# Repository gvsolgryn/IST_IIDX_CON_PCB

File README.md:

# IST_IIDX_CON_PCB
ist 몰에서 만든 iidx 컨트롤러 PCB 딜레이가 너무 심해서 우리 기합찬 육군(만기전역)들이 설계하기로 하였다

## 기합찬 준비운동

1. 일단 KiCAD를 받는다
2. `git` 을 다운로드 받는다
3. `git clone https://github.com/gvsolgryn/IST_IIDX_CON_PCB.git` 을 하여 우리 기합찬 PCB 프로젝트를 다운로드 받는다
4. KiCAD를 실행 시킨 뒤 프로젝트를 연다
5. 불만이 있으면 KiCAD를 이용해서 PCB 다 수정해서 머지? 요청 하면 우리 기합찬 육군들이 업데이트를 해주도록 하겠다

## 악! PCB Gerber을 이용하여 PCB를 출력하고싶어 해병님!!
1. https://jlcpcb.com/ 에 방문한다
2. gerber.zip 을 Add Gerber File 에 드래그 엔 드롭 한다
3. 결제한다!

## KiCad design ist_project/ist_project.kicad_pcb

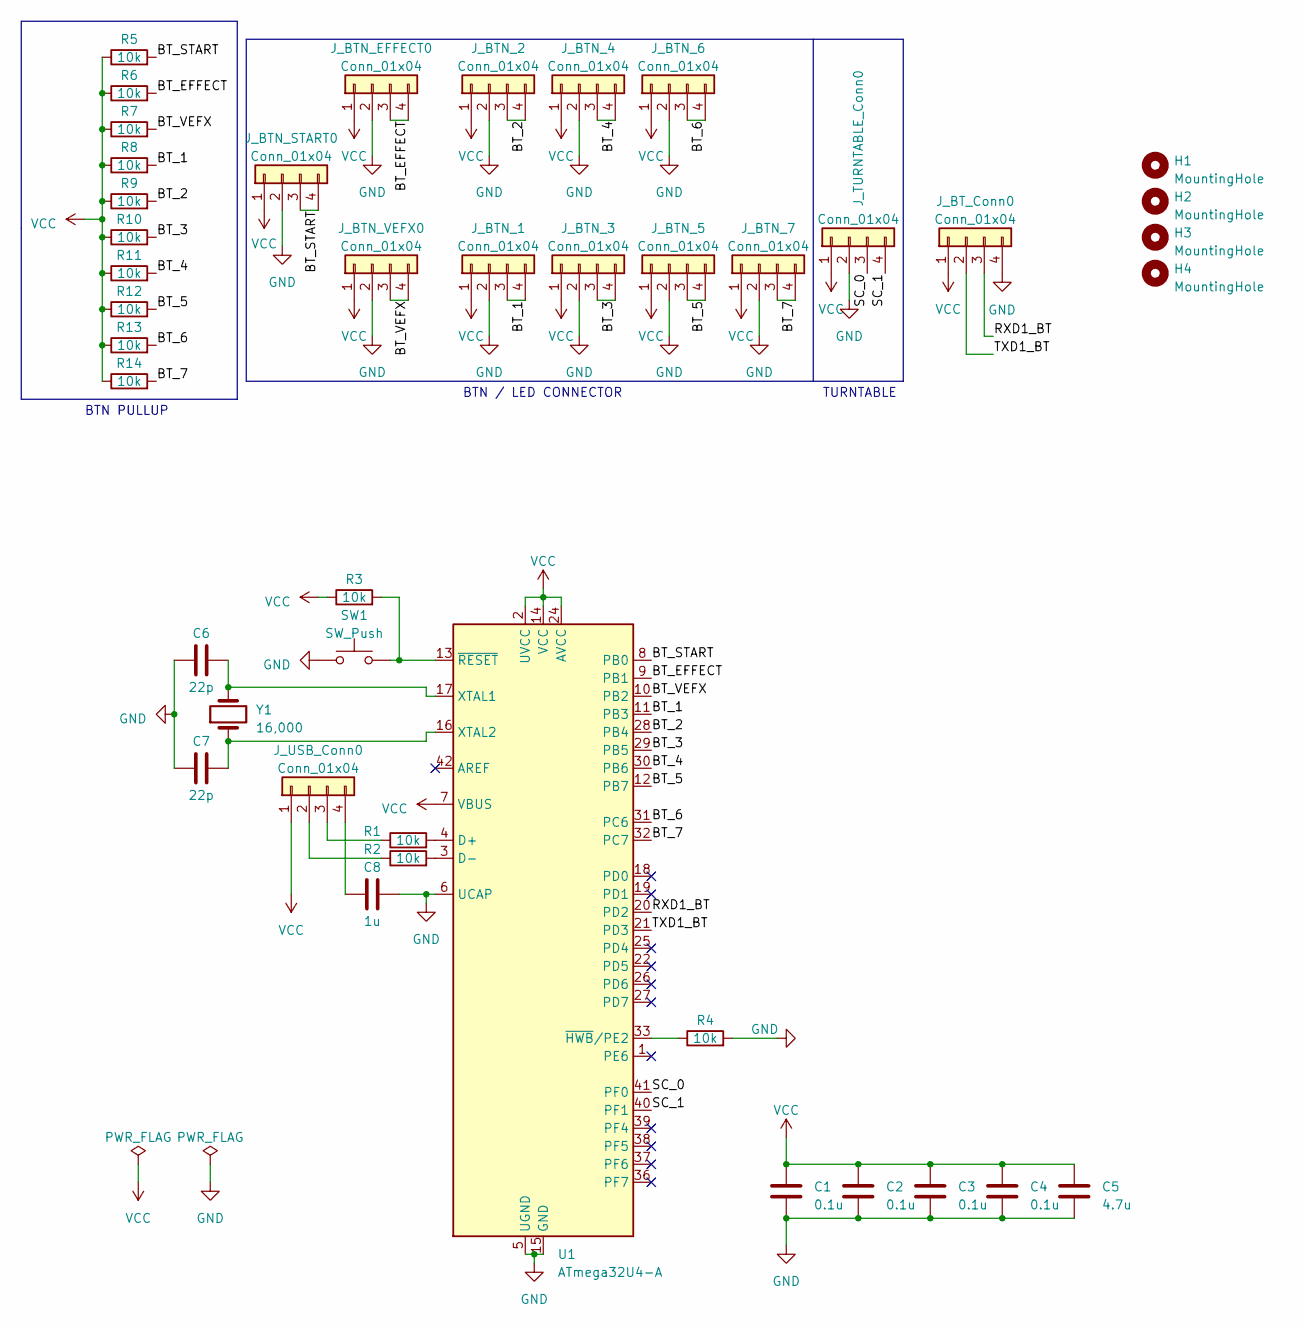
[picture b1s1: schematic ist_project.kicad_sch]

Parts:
C1, C2, C3, C4: 0.1u; C_0805_2012Metric_Pad1.18x1.45mm_HandSolder
C5: 4.7u; C_0805_2012Metric_Pad1.18x1.45mm_HandSolder
C6, C7: 22p; C_0805_2012Metric_Pad1.18x1.45mm_HandSolder
C8: 1u; C_0805_2012Metric_Pad1.18x1.45mm_HandSolder
H1, H2, H3, H4: MountingHole; MountingHole_3.2mm_M3_ISO7380_Pad_TopOnly
J_BTN_1, J_BTN_2, J_BTN_3, J_BTN_4, J_BTN_5, J_BTN_6, J_BTN_7: Conn_01x04; Molex_SPOX_5267-04A_1x04_P2.50mm_Vertical
J_BTN_EFFECT0: Conn_01x04; Molex_SPOX_5267-04A_1x04_P2.50mm_Vertical
J_BTN_START0: Conn_01x04; Molex_SPOX_5267-04A_1x04_P2.50mm_Vertical
J_BTN_VEFX0: Conn_01x04; Molex_SPOX_5267-04A_1x04_P2.50mm_Vertical
J_BT_Conn0: Conn_01x04; Molex_SPOX_5267-04A_1x04_P2.50mm_Vertical
J_TURNTABLE_Conn0: Conn_01x04; Molex_SPOX_5267-04A_1x04_P2.50mm_Vertical
J_USB_Conn0: Conn_01x04; Molex_SPOX_5267-04A_1x04_P2.50mm_Vertical
R1, R2, R3, R4, R5, R6, R7, R8, R9, R10, R11, R12, R13, R14: 10k; R_0805_2012Metric_Pad1.20x1.40mm_HandSolder
SW1: SW_Push; SW_Push_1P1T_NO_6x6mm_H9.5mm
U1: ATmega32U4-A; TQFP-44_10x10mm_P0.8mm
Y1: 16,000; Crystal_SMD_HC49-SD_HandSoldering

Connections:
/BT_1: J_BTN_1.3, J_BTN_1.4, R8.2, U1.11 (PB3)
/BT_2: J_BTN_2.3, J_BTN_2.4, R9.2, U1.28 (PB4)
/BT_3: J_BTN_3.3, J_BTN_3.4, R10.2, U1.29 (PB5)
/BT_4: J_BTN_4.3, J_BTN_4.4, R11.2, U1.30 (PB6)
/BT_5: J_BTN_5.3, J_BTN_5.4, R12.2, U1.12 (PB7)
/BT_6: J_BTN_6.3, J_BTN_6.4, R13.2, U1.31 (PC6)
/BT_7: J_BTN_7.3, J_BTN_7.4, R14.2, U1.32 (PC7)
/BT_EFFECT: J_BTN_EFFECT0.3, J_BTN_EFFECT0.4, R6.2, U1.9 (PB1)
/BT_START: J_BTN_START0.3, J_BTN_START0.4, R5.2, U1.8 (PB0)
/BT_VEFX: J_BTN_VEFX0.3, J_BTN_VEFX0.4, R7.2, U1.10 (PB2)
/RXD1_BT: J_BT_Conn0.3, U1.20 (PD2)
/SC_0: J_TURNTABLE_Conn0.3, U1.41 (PF0)
/SC_1: J_TURNTABLE_Conn0.4, U1.40 (PF1)
/TXD1_BT: J_BT_Conn0.2, U1.21 (PD3)
GND: C1.2, C2.2, C3.2, C4.2, C5.2, C6.1, C7.2, C8.2, J_BTN_1.2, J_BTN_2.2, J_BTN_3.2, J_BTN_4.2, J_BTN_5.2, J_BTN_6.2, J_BTN_7.2, J_BTN_EFFECT0.2, J_BTN_START0.2, J_BTN_VEFX0.2, J_BT_Conn0.4, J_TURNTABLE_Conn0.2, R4.2, SW1.1, U1.5 (UGND), U1.6 (UCAP), U1.15 (GND), U1.23 (GND), U1.35 (GND), U1.43 (GND)
unnamed: J_USB_Conn0.2, R2.1
unnamed: J_USB_Conn0.3, R1.1
unnamed: C8.1, J_USB_Conn0.4
unnamed: R1.2, U1.4 (D+)
unnamed: R2.2, U1.3 (D-)
unnamed: C6.2, U1.17 (XTAL1), Y1.2
unnamed: C7.1, U1.16 (XTAL2), Y1.1
unnamed: R4.1, U1.33 (~HWB/PE2)
unnamed: R3.2, SW1.2, U1.13 (~RESET)
VCC: C1.1, C2.1, C3.1, C4.1, C5.1, J_BTN_1.1, J_BTN_2.1, J_BTN_3.1, J_BTN_4.1, J_BTN_5.1, J_BTN_6.1, J_BTN_7.1, J_BTN_EFFECT0.1, J_BTN_START0.1, J_BTN_VEFX0.1, J_BT_Conn0.1, J_TURNTABLE_Conn0.1, J_USB_Conn0.1, R3.1, R5.1, R6.1, R7.1, R8.1, R9.1, R10.1, R11.1, R12.1, R13.1, R14.1, U1.2 (UVCC), U1.7 (VBUS), U1.14 (VCC), U1.24 (AVCC), U1.34 (VCC), U1.44 (AVCC)

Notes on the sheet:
TURNTABLE
BTN / LED CONNECTOR
BTN PULLUP

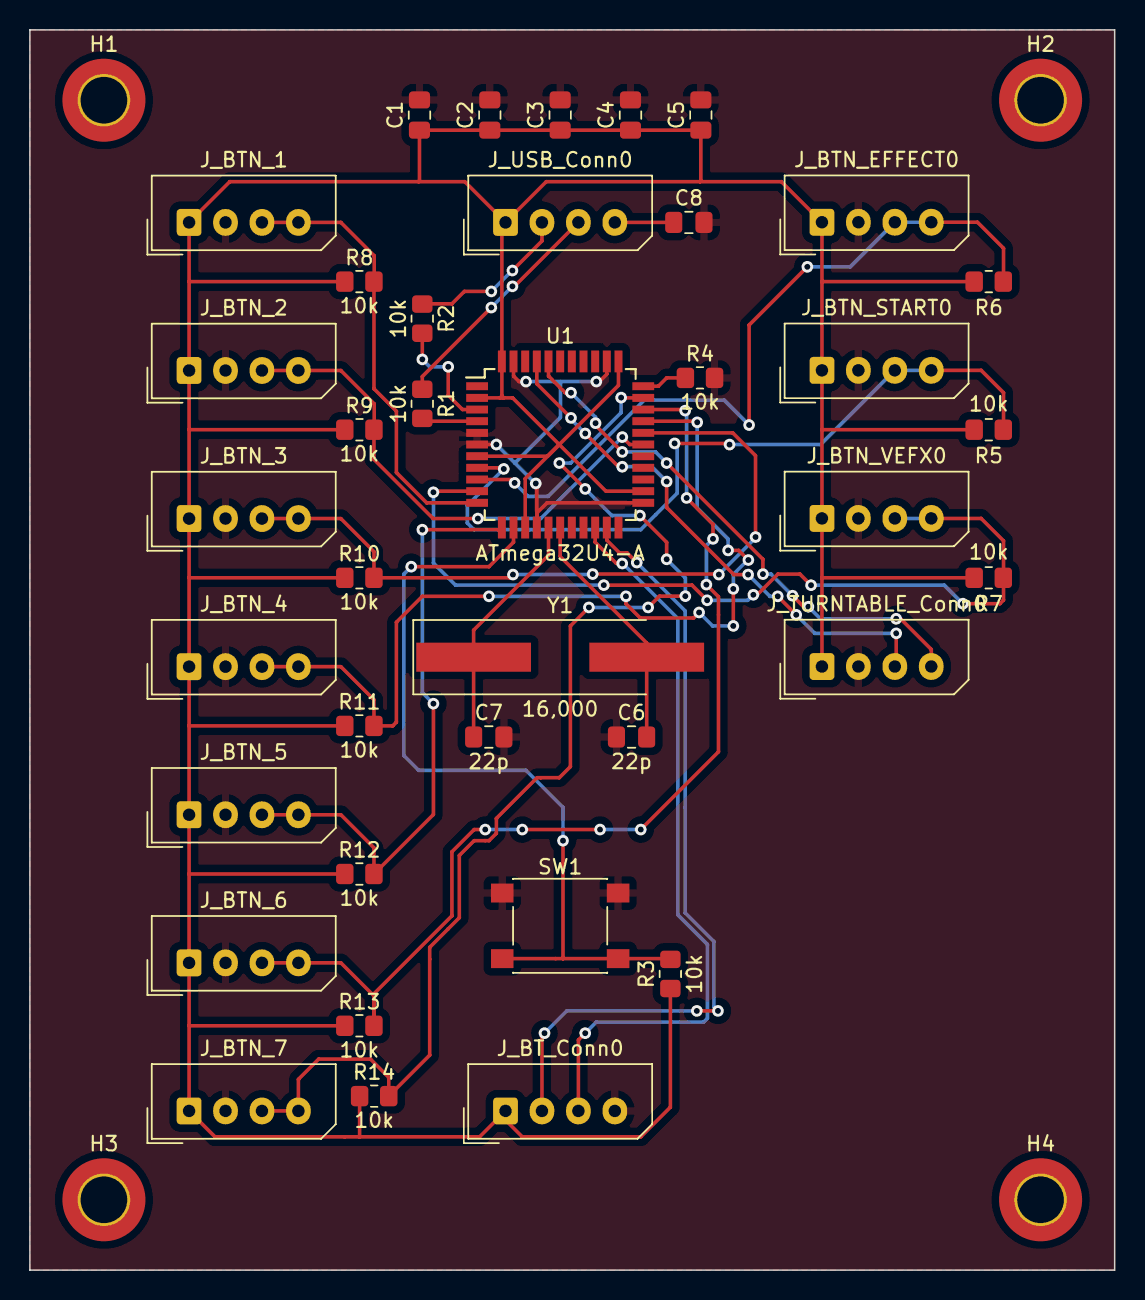
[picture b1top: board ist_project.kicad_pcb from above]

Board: 2 copper layers, 74.4 x 85.1 mm, 42 parts (0 on the bottom side), 25 nets.

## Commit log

2022-10-24 Add KiCAD Project
2023-01-03 Add Pro Micro Library & footprint
2023-04-13 회로도 완성 (Atmega32u4 Base)
2023-04-13 회로도 수정 / pcb 작업중
2023-04-16 PCB 그리기 완료 / Mount Hole 추가
2023-04-16 gitignore 수정
